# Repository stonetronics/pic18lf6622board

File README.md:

# pic18lf6622board

A Arduino-like Microcontroller board with a PIC18LF6622 microcontroller

#### Features: #####

- PIC18LF6622 Microcontroller
 - PICKit header
 - 12MHz Crystal
- FT230XQ USB/Serial controller
 - Micro-USB connector
 - RX/TX disconnectable
- 5V and 3V3 Regulator
 - AMS1117: 1A
 - VDD and AVDD connectable to 5V, 3V3 and VUSB
- All useful pins on the controller are broken out on pinheaders
- 2 Layer Board
- drawn in KiCad
 
The Board is built to be programmed with a PICKit, altough one could also build a serial bootloader.

### Uart Driver ###
There is a MPLAB X Project UartTest.X that contains a test for a library that lets you use the uart. The driver is interrupt-driven and uses circular buffers to store incoming and outgoing data while not blocking the main program flow. This project can be used as template with integrated uart support + circular buffer middleware.

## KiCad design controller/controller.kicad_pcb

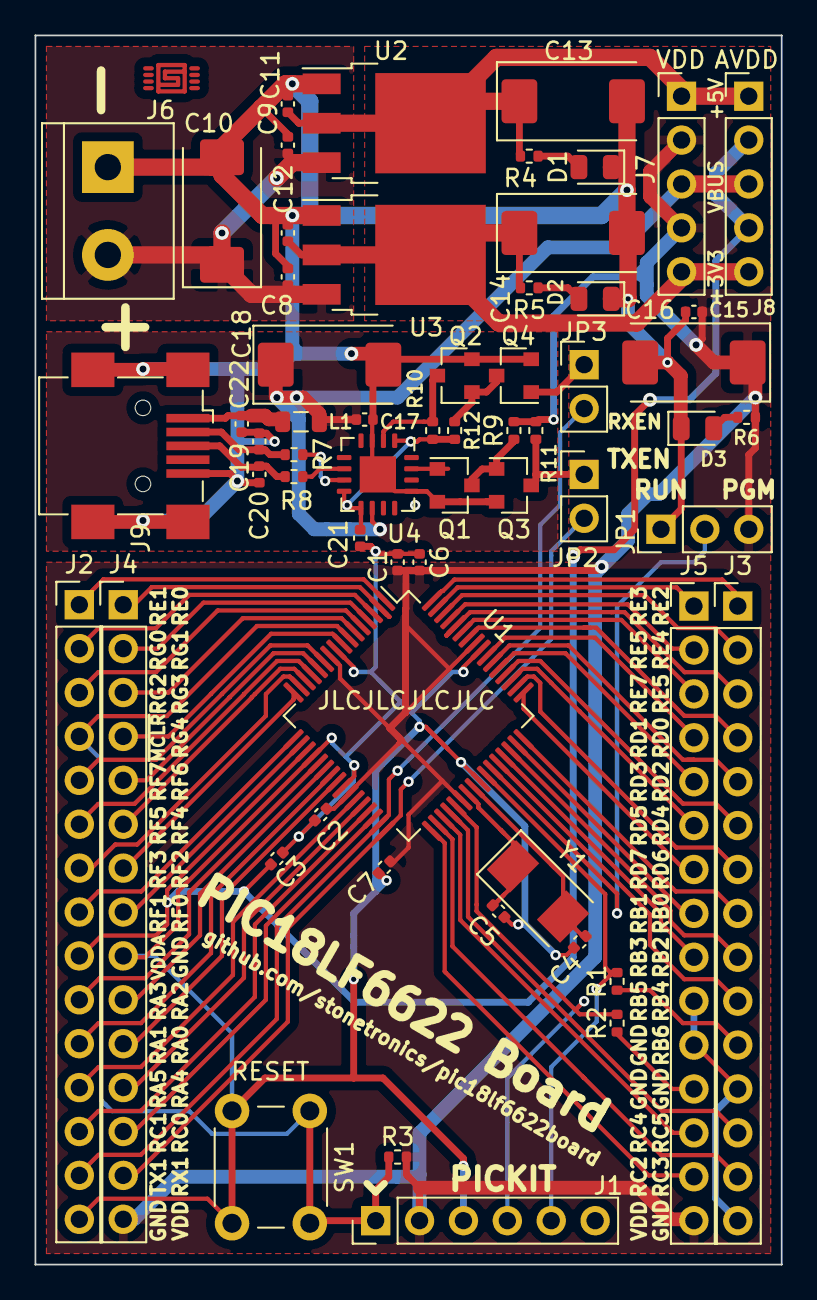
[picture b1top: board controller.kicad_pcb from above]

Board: 2 copper layers, 43.2 x 71.1 mm, 60 parts (0 on the bottom side), 78 nets.

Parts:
C1, C2, C3, C6, C7, C8, C9, C11, C12, C15, C17, C21: 100n; C_0402_1005Metric
C4, C5: 22p; C_0402_1005Metric
C10, C13, C14, C16, C18: 150uF; CP_EIA-7343-31_Kemet-D
C19, C20: 47p; C_0402_1005Metric
C22: 10n; C_0402_1005Metric
D1, D2, D3: LED; LED_0805_2012Metric
J1: PICKIT; PinHeader_1x06_P2.54mm_Vertical
J2: IO_A; PinHeader_1x15_P2.54mm_Vertical
J3: IO_C; PinHeader_1x15_P2.54mm_Vertical
J4: IO_B; PinHeader_1x15_P2.54mm_Vertical
J5: IO_D; PinHeader_1x15_P2.54mm_Vertical
J6: POWER; TerminalBlock_bornier-2_P5.08mm
J7: VDD; PinHeader_1x05_P2.54mm_Vertical
J8: AVDD; PinHeader_1x05_P2.54mm_Vertical
J9: USB_B_Micro; USB_Mini-B_Wuerth_65100516121_Horizontal
JP1: PGM/RUN; PinHeader_1x03_P2.54mm_Vertical
JP2: TX; PinHeader_1x02_P2.54mm_Vertical
JP3: RX; PinHeader_1x02_P2.54mm_Vertical
L1: 600Ohm 100MHz; L_0805_2012Metric
Q1, Q2, Q3, Q4: BSS138; SOT-23
R1, R2: 100R; R_0402_1005Metric
R3: 10k; R_0402_1005Metric
R4, R6: 270R; R_0402_1005Metric
R5: 120R; R_0402_1005Metric
R7, R8: 27R; R_0402_1005Metric
R9, R10, R11, R12: 4k7; R_0402_1005Metric
SW1: Reset; SW_PUSH_6mm_H5mm
U1: PIC18LF6622-IPT; TQFP-64_10x10mm_P0.5mm
U2: AMS1117-5.0; TO-252-3_TabPin2
U3: AMS1117CD-3.3; TO-252-3_TabPin2
U4: FT230XQ; QFN-16-1EP_4x4mm_P0.65mm_EP2.1x2.1mm
Y1: 12 MHz; Crystal_SMD_Abracon_ABM3-2Pin_5.0x3.2mm

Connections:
+3V3: C12.2, C14.1, J7.5, J8.5, R5.1, U3.2
+5V: C11.2, C13.1, J7.1, J8.1, R4.1, U2.2
/PGC: J1.5, R1.2, U1.42
/PGD: J1.4, R2.2, U1.37
/PGM: JP1.2, U1.43
/RA0: J4.11, U1.24
/RA1: J2.11, U1.23
/RA2: J4.10, U1.22
/RA3: J2.10, U1.21
/RA4: J4.12, U1.28
/RA5: J2.12, U1.27
/RB0: J3.8, U1.48
/RB1: J5.8, U1.47
/RB2: J3.9, U1.46
/RB3: J5.9, U1.45
/RB4: J3.10, U1.44
/RC0: J4.13, U1.30
/RC1: J2.13, U1.29
/RC2: J5.14, U1.33
/RC3: J3.14, U1.34
/RC4: J5.13, U1.35
/RC5: J3.13, U1.36
/RD0: J3.4, U1.58
/RD1: J5.4, U1.55
/RD2: J3.5, U1.54
/RD3: J5.5, U1.53
/RD4: J3.6, U1.52
/RD5: J5.6, U1.51
/RD6: J3.7, U1.50
/RD7: J5.7, U1.49
/RE0: J4.1, U1.2
/RE1: J2.1, U1.1
/RE2: J3.1, U1.64
/RE3: J5.1, U1.63
/RE4: J3.2, U1.62
/RE5: J5.2, U1.61
/RE6: J3.3, U1.60
/RE7: J5.3, U1.59
/RF0: J4.8, U1.18
/RF1: J2.8, U1.17
/RF2: J4.7, U1.16
/RF3: J2.7, U1.15
/RF4: J4.6, U1.14
/RF5: J2.6, U1.13
/RF6: J4.5, U1.12
/RF7: J2.5, U1.11
/RG0: J2.2, U1.3
/RG1: J4.2, U1.4
/RG2: J2.3, U1.5
/RG3: J4.3, U1.6
/RG4: J4.4, U1.8
/~MCLR~: J1.1, J2.4, R3.1, SW1.1, U1.7
GND: C1.1, C2.1, C3.1, C4.1, C5.1, C6.1, C7.1, C8.1, C9.1, C10.2, C11.1, C12.1, C13.2, C14.2, C15.1, C16.2, C17.1, C18.2, C19.1, C20.1, C21.1, C22.1, D1.1, D2.1, D3.1, J1.3, J2.15, J3.12, J3.15, J4.9, J5.10, J5.11, J6.1, J9.5, J9.6, JP1.1, Q1.2, Q2.2, Q3.2, Q4.2, SW1.2, U1.9, U1.20, U1.25, U1.41, U1.56, U2.1, U3.1, U4.3, U4.13, U4.17
unnamed: C4.2, U1.40, Y1.2
unnamed: C5.2, U1.39, Y1.1
unnamed: C8.2, C9.2, C10.1, J6.2, U2.3, U3.3
unnamed: C19.2, J9.2, R7.2
unnamed: C20.2, J9.3, R8.1
unnamed: C21.2, R10.2, R12.2, U4.1, U4.8, U4.9
unnamed: C22.2, J9.1, L1.2
unnamed: D1.2, R4.2
unnamed: D2.2, R5.2
unnamed: D3.2, R6.2
unnamed: J3.11, R1.1
unnamed: J5.12, R2.1
unnamed: JP2.1, Q3.3, R11.1
unnamed: JP3.1, Q4.1
unnamed: Q1.1, U4.15
unnamed: Q1.3, Q3.1, R9.1
unnamed: Q2.1, Q4.3, R12.1
unnamed: Q2.3, R10.1, U4.2
unnamed: R7.1, U4.7
unnamed: R8.2, U4.6
RX1: J4.14, JP2.2, U1.32
TX1: J2.14, JP3.2, U1.31
VBUS: C17.2, C18.1, J7.3, J8.3, L1.1, U4.10
VDD: C1.2, C2.2, C6.2, C7.2, C15.2, C16.1, J1.2, J4.15, J5.15, J7.2, J7.4, JP1.3, R3.2, R6.1, R9.2, R11.2, U1.10, U1.26, U1.38, U1.57
VDDA: C3.2, J2.9, J8.2, J8.4, U1.19

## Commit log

2020-11-03 Create LICENSE
2020-11-21 add uart driver
2020-11-21 add gitignore
2020-11-21 modify gitignore
2020-11-23 fix bug with displaying '0', disable watchdog in config setup
